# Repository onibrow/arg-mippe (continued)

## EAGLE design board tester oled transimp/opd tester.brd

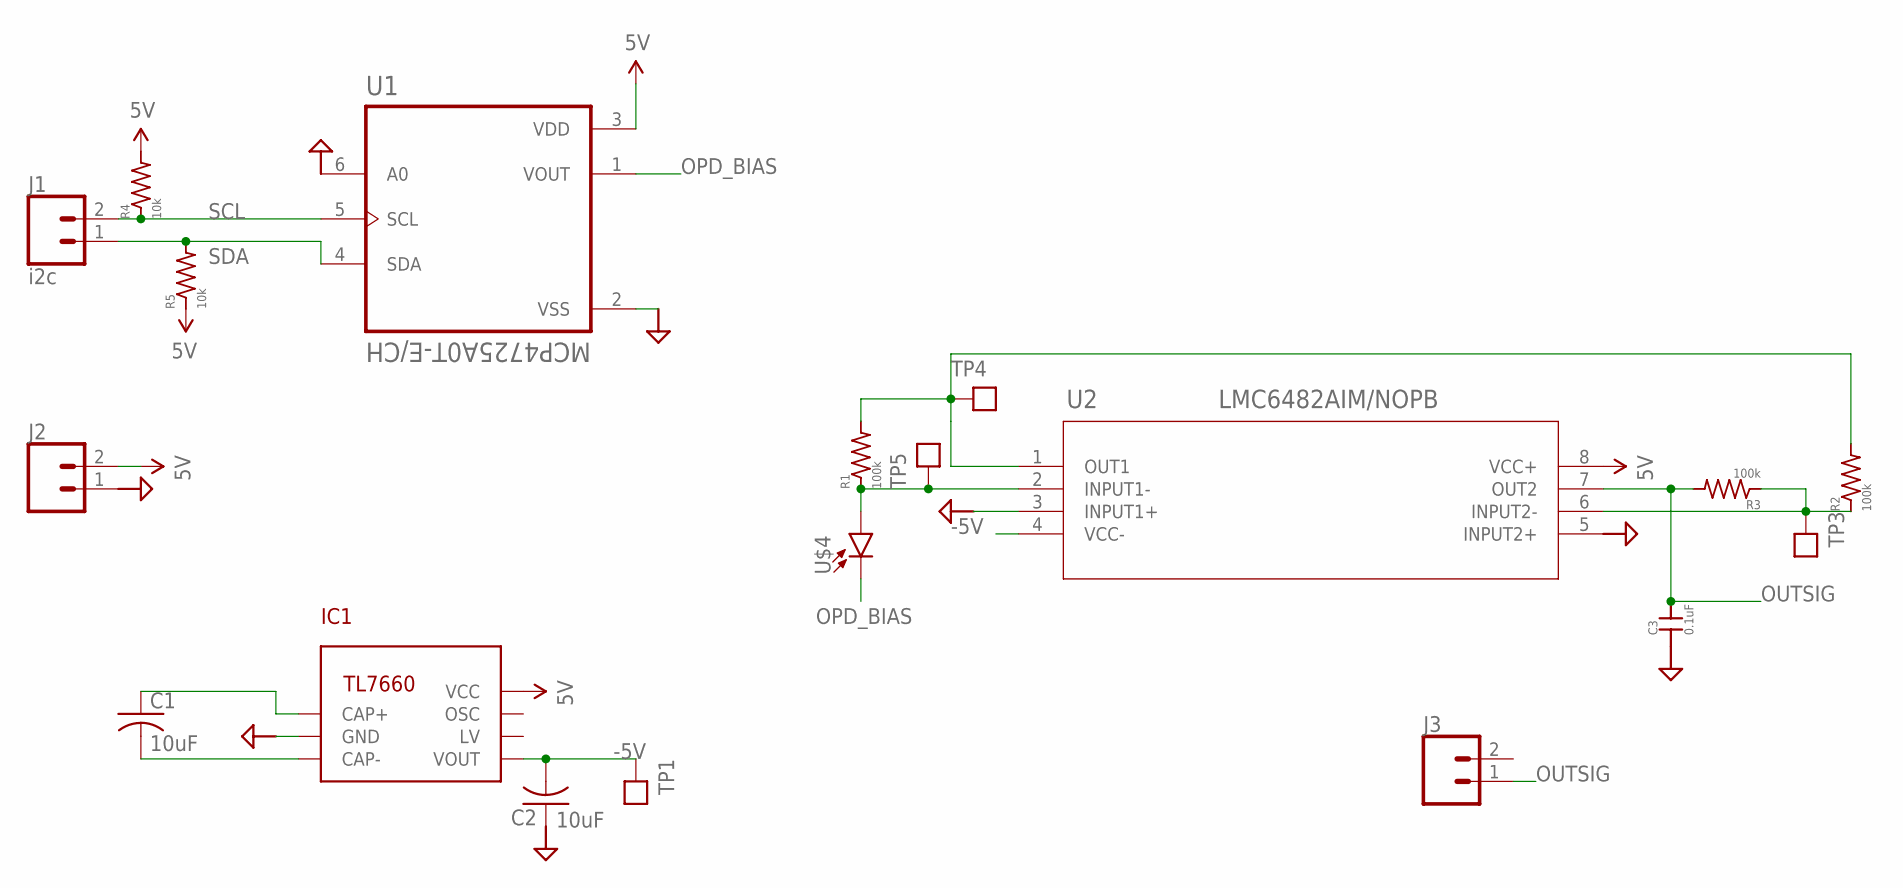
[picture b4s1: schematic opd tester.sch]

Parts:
C1, C2: 10uF; CAP_3MM
C3: 0.1uF; 0603-CAP
IC1: TL7660; 8SOICW
J1: i2c; 1X02
J2, J3: CONN_02; 1X02
R1, R2, R3: 100k; 0603-RES
R4, R5: 10k; 0603-RES
TP1, TP3, TP4, TP5: TEST_POINTTHRU; TEST_POINT
U1: MCP4725A0T-E/CH; SOT95P270X145-6N
U2: LMC6482AIM/NOPB; M08A
U$4: XDCR_SFH_229

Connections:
5V: IC1.8 (VCC), J2.2, R4.2, R5.1, U1.3 (VDD), U2.8 (VCC+)
-5V: C2.NEG, IC1.5 (VOUT), TP1.1, U2.4 (VCC-)
GND: C2.POS, C3.1, IC1.3 (GND), J2.1, U1.2 (VSS), U1.6 (A0), U2.3 (INPUT1+), U2.5 (INPUT2+)
unnamed: C1.POS, IC1.2 (CAP+)
unnamed: C1.NEG, IC1.4 (CAP-)
unnamed 5: R1.1, TP5.1, U2.2 (INPUT1-), U$4.1 (A); also elsewhere on the board
unnamed 6: R1.2, R2.2, TP4.1, U2.1 (OUT1); also elsewhere on the board
unnamed: R2.1, R3.1, TP3.1, U2.6 (INPUT2-)
OPD_BIAS: U1.1 (VOUT), U$4.2 (C)
OUTSIG: C3.2, J3.1, R3.2, U2.7 (OUT2)
SCL: J1.2, R4.1, U1.5 (SCL)
SDA: J1.1, R5.2, U1.4 (SDA)

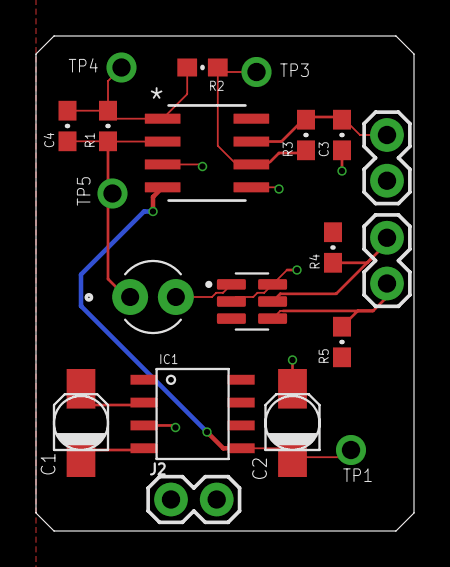
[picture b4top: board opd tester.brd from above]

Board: 2 copper layers, 21.0 x 27.5 mm, 20 parts (0 on the bottom side), 12 nets.

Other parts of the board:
C4: 0.1uF; 0603-CAP

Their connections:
unnamed 5: C4.1; also elsewhere on the board
unnamed 6: C4.2; also elsewhere on the board

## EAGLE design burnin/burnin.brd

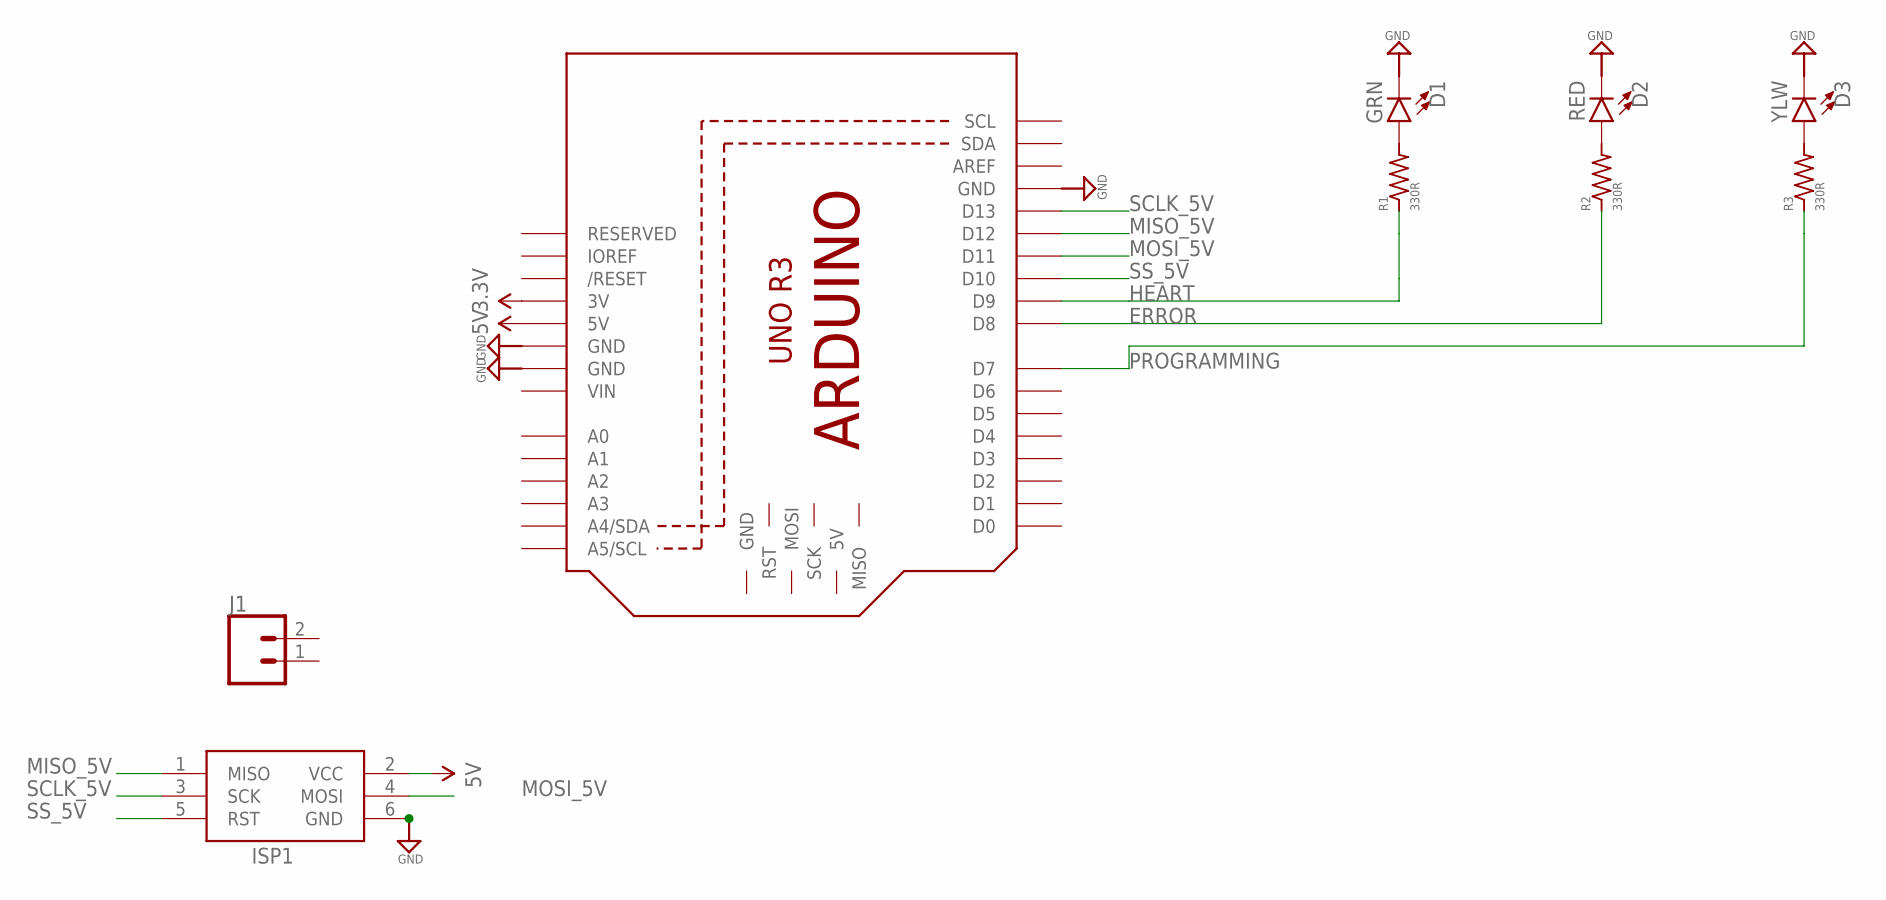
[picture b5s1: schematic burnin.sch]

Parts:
D1: GRN; LED-0603
D2: RED; LED-0603
D3: YLW; LED-0603
ISP1: AVRISP-6; AVRISP
J1: CONN_02; 1X02
M1: ARDUINO_R3_ICSP_NODIM; ARDUINOR3_ICSP_NODIM
R1, R2, R3: 330R; 0603-RES

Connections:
3.3V: M1.3V
5V: ISP1.2 (VCC), M1.5V
ERROR: M1.D8, R2.1
GND: D1.C, D2.C, D3.C, ISP1.6 (GND), M1.GND, M1.GND@1 (GND), M1.GND@3 (GND)
HEART: M1.D9, R1.1
MISO_5V: ISP1.1 (MISO), M1.D12
MOSI_5V: ISP1.4 (MOSI), M1.D11
unnamed: D1.A, R1.2
unnamed: D2.A, R2.2
unnamed: D3.A, R3.2
PROGRAMMING: M1.D7, R3.1
SCLK_5V: ISP1.3 (SCK), M1.D13
SS_5V: ISP1.5 (RST), M1.D10
VIN: M1.VIN

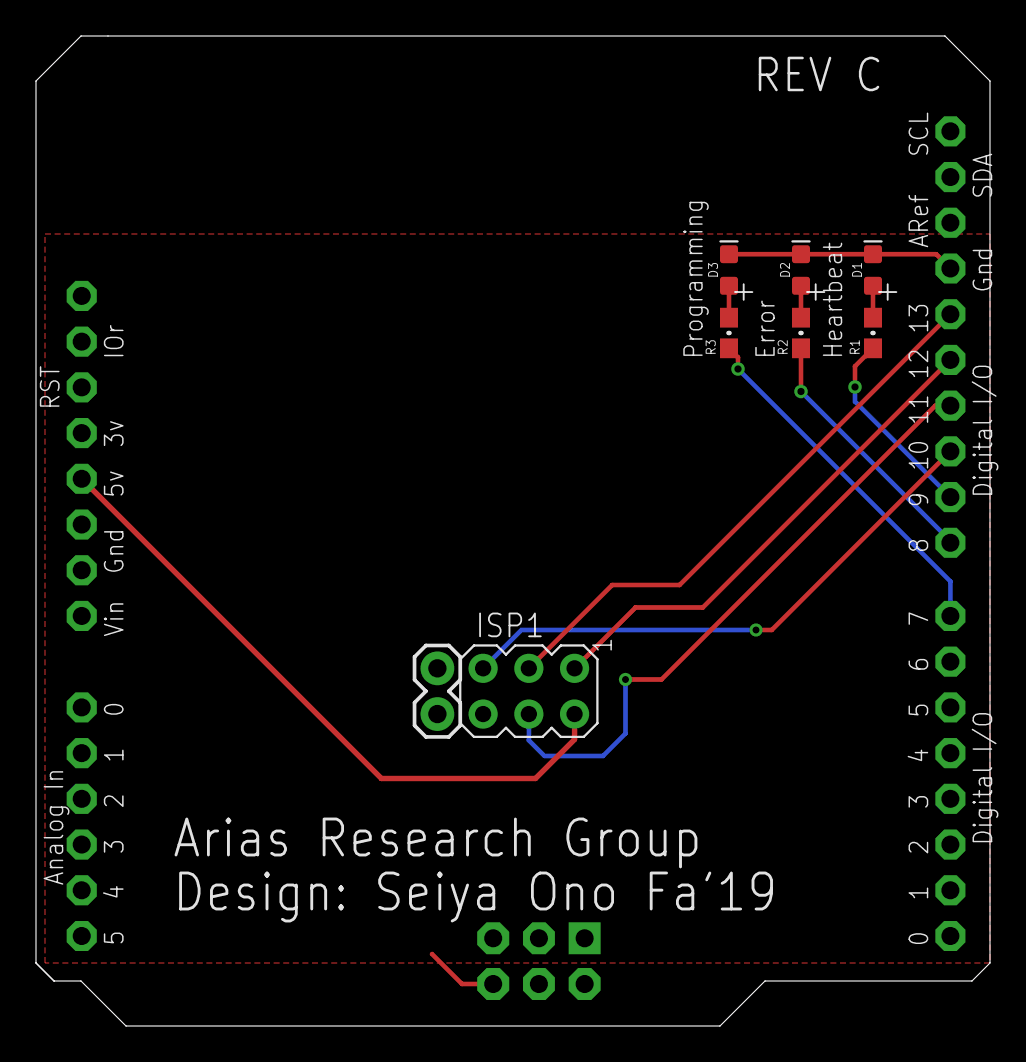
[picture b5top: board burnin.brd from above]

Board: 2 copper layers, 53.0 x 55.0 mm, 9 parts (0 on the bottom side), 12 nets.

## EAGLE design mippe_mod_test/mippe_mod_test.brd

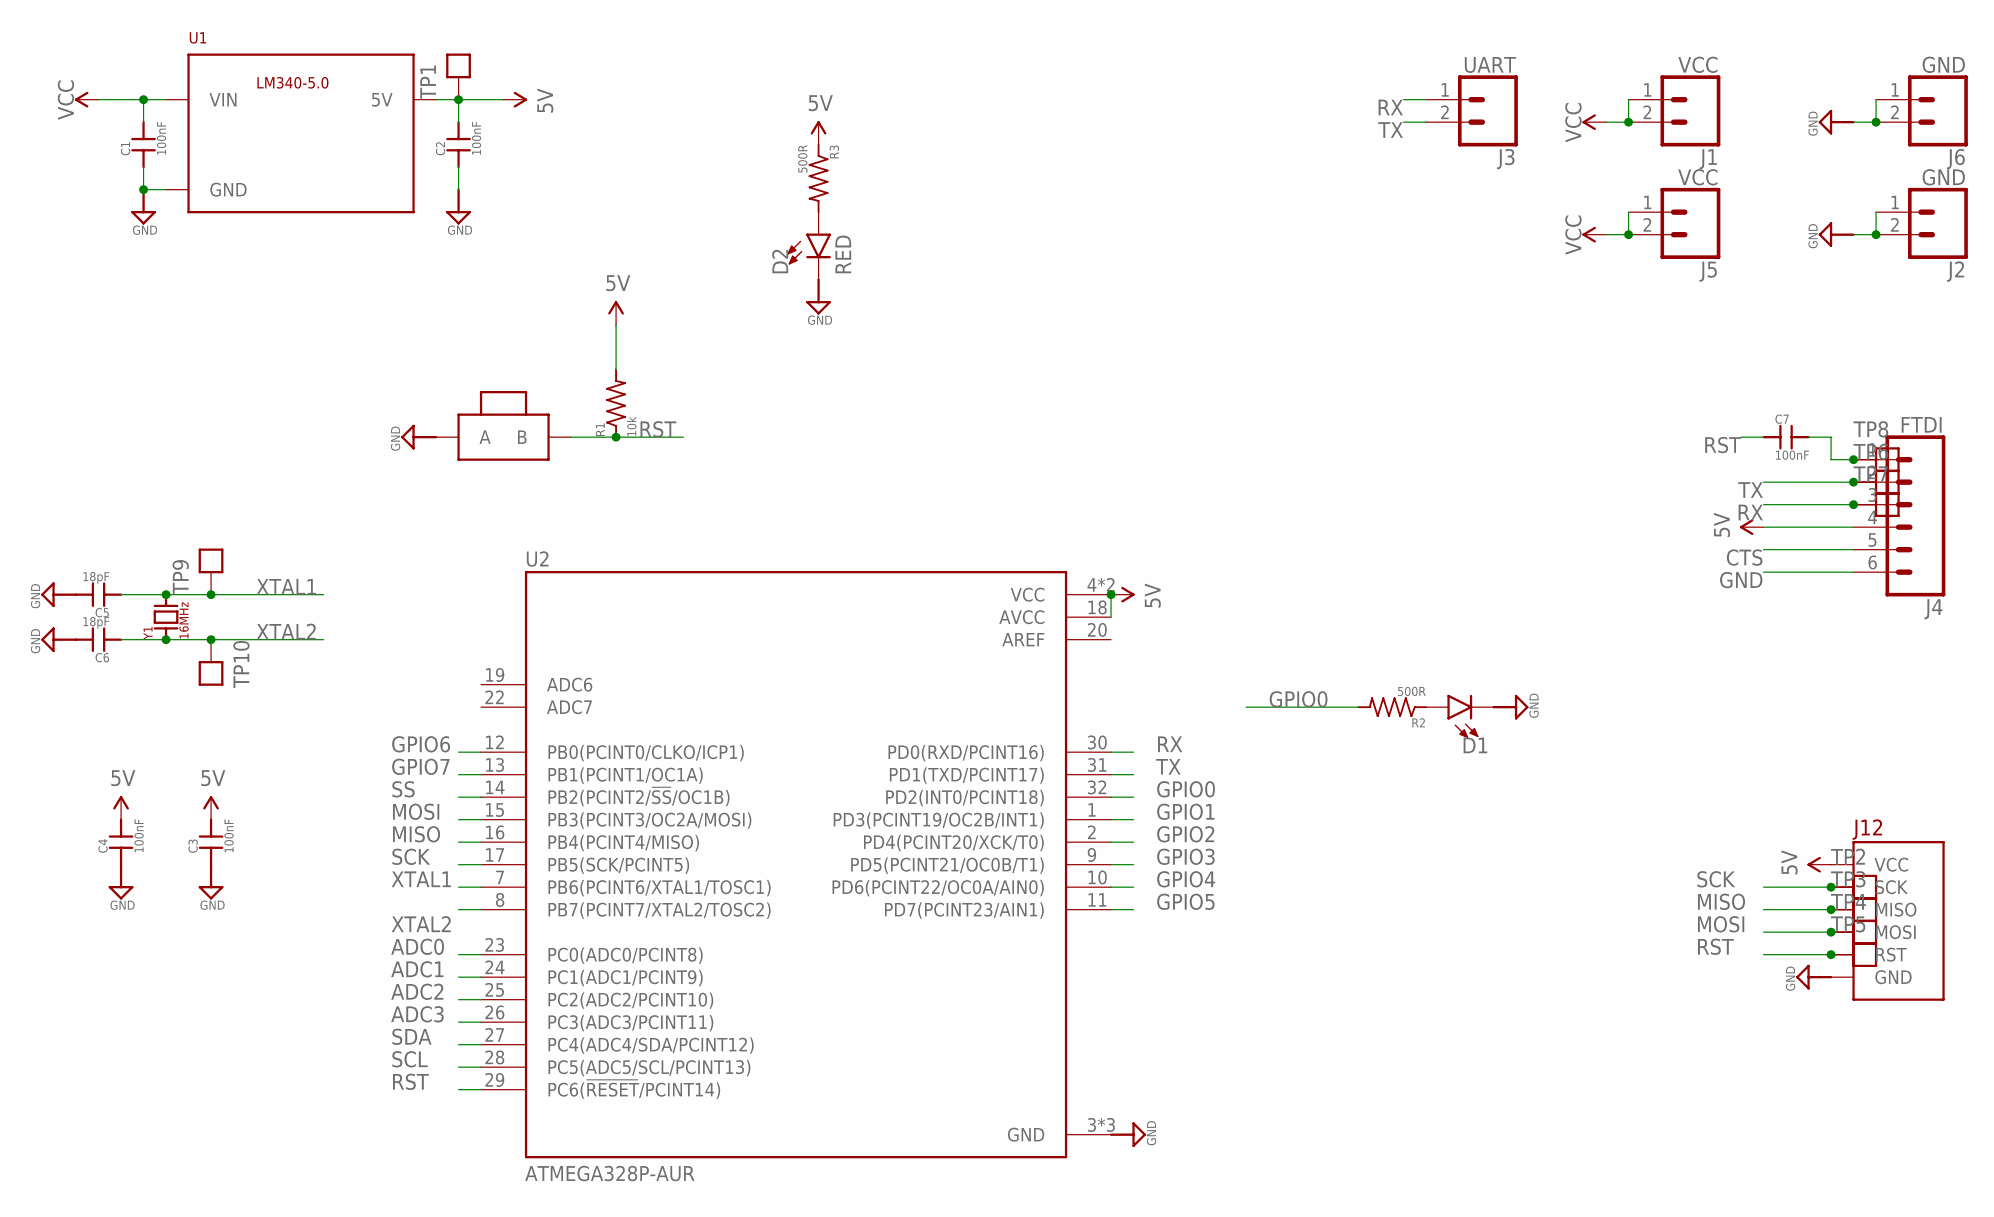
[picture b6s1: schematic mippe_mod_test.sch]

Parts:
C1, C2, C3, C4, C7: 100nF; 0402-CAP
C5, C6: 18pF; 0402-CAP
D1: LED0603; LED-0603
D2: RED; LED-0603
J1, J5: VCC; 1X02
J2, J6: GND; 1X02
J3: UART; 1X02
J4: FTDI; 1X06_NO_SILK
J12: BURNIN
R1: 10k; R0402
R2, R3: 500R; R0402
SW1: BTN-PTS810; BTN_PTS810
TP1, TP2, TP3, TP4, TP5, TP6, TP7, TP8, TP9, TP10: TEST_POINTTHRU; TEST_POINT
U1: LM340MPX-5.0230; SOT230P700X180-4N
U2: ATMEGA328P-AUR; QFP80P900X900X120-32N
Y1: 16MHz; XTAL500X320X130N

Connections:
5V: C2.2, C3.2, C4.2, J4.4, J12.3.3V (VCC), R1.2, R3.1, TP1.1, U1.3 (5V), U2.4 (VCC), U2.6 (VCC), U2.18 (AVCC)
ADC0: U2.23 (PC0(ADC0/PCINT8))
ADC1: U2.24 (PC1(ADC1/PCINT9))
ADC2: U2.25 (PC2(ADC2/PCINT10))
ADC3: U2.26 (PC3(ADC3/PCINT11))
AREF: U2.20 (AREF)
CTS: J4.5
GND: C1.1, C2.1, C3.1, C4.1, C5.2, C6.2, D1.C, D2.C, J2.1, J2.2, J4.6, J6.1, J6.2, J12.GND, SW1.1 (A), SW1.2 (A), U1.2 (GND), U1.4 (GND), U2.3 (GND), U2.5 (GND), U2.21 (GND)
GPIO0: R2.2, U2.32 (PD2(INT0/PCINT18))
GPIO1: U2.1 (PD3(PCINT19/OC2B/INT1))
GPIO2: U2.2 (PD4(PCINT20/XCK/T0))
GPIO3: U2.9 (PD5(PCINT21/OC0B/T1))
GPIO4: U2.10 (PD6(PCINT22/OC0A/AIN0))
GPIO5: U2.11 (PD7(PCINT23/AIN1))
GPIO6: U2.12 (PB0(PCINT0/CLKO/ICP1))
GPIO7: U2.13 (PB1(PCINT1/OC1A))
MISO: J12.MISO, TP3.1, U2.16 (PB4(PCINT4/MISO))
MOSI: J12.MOSI, TP4.1, U2.15 (PB3(PCINT3/OC2A/MOSI))
unnamed: D1.A, R2.1
unnamed: D2.A, R3.2
unnamed: C7.2, J4.1, TP8.1
RST: C7.1, J12.RST, R1.1, SW1.3 (B), SW1.4 (B), TP5.1, U2.29 (PC6(!RESET!/PCINT14))
RX: J3.1, J4.3, TP7.1, U2.30 (PD0(RXD/PCINT16))
SCK: J12.SCK, TP2.1, U2.17 (PB5(SCK/PCINT5))
SCL: U2.28 (PC5(ADC5/SCL/PCINT13))
SDA: U2.27 (PC4(ADC4/SDA/PCINT12))
SS: U2.14 (PB2(PCINT2/!SS!/OC1B))
TX: J3.2, J4.2, TP6.1, U2.31 (PD1(TXD/PCINT17))
VCC: C1.2, J1.1, J1.2, J5.1, J5.2, U1.1 (VIN)
XTAL1: C5.1, TP9.1, U2.7 (PB6(PCINT6/XTAL1/TOSC1)), Y1.2 (B)
XTAL2: C6.1, TP10.1, U2.8 (PB7(PCINT7/XTAL2/TOSC2)), Y1.1 (A)

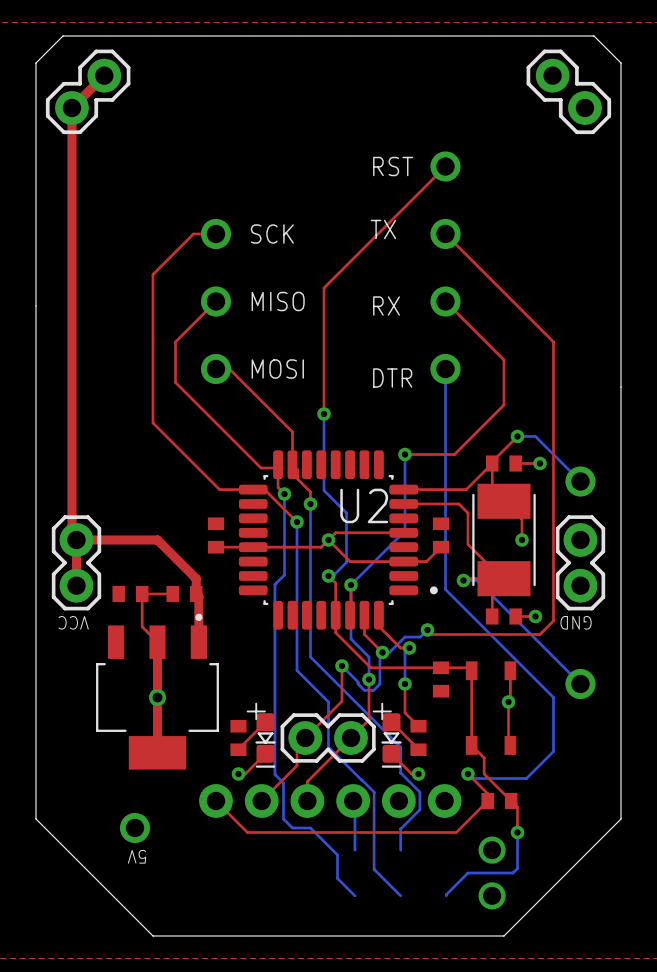
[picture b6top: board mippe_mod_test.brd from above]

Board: 2 copper layers, 32.5 x 50.0 mm, 33 parts (0 on the bottom side), 15 nets.

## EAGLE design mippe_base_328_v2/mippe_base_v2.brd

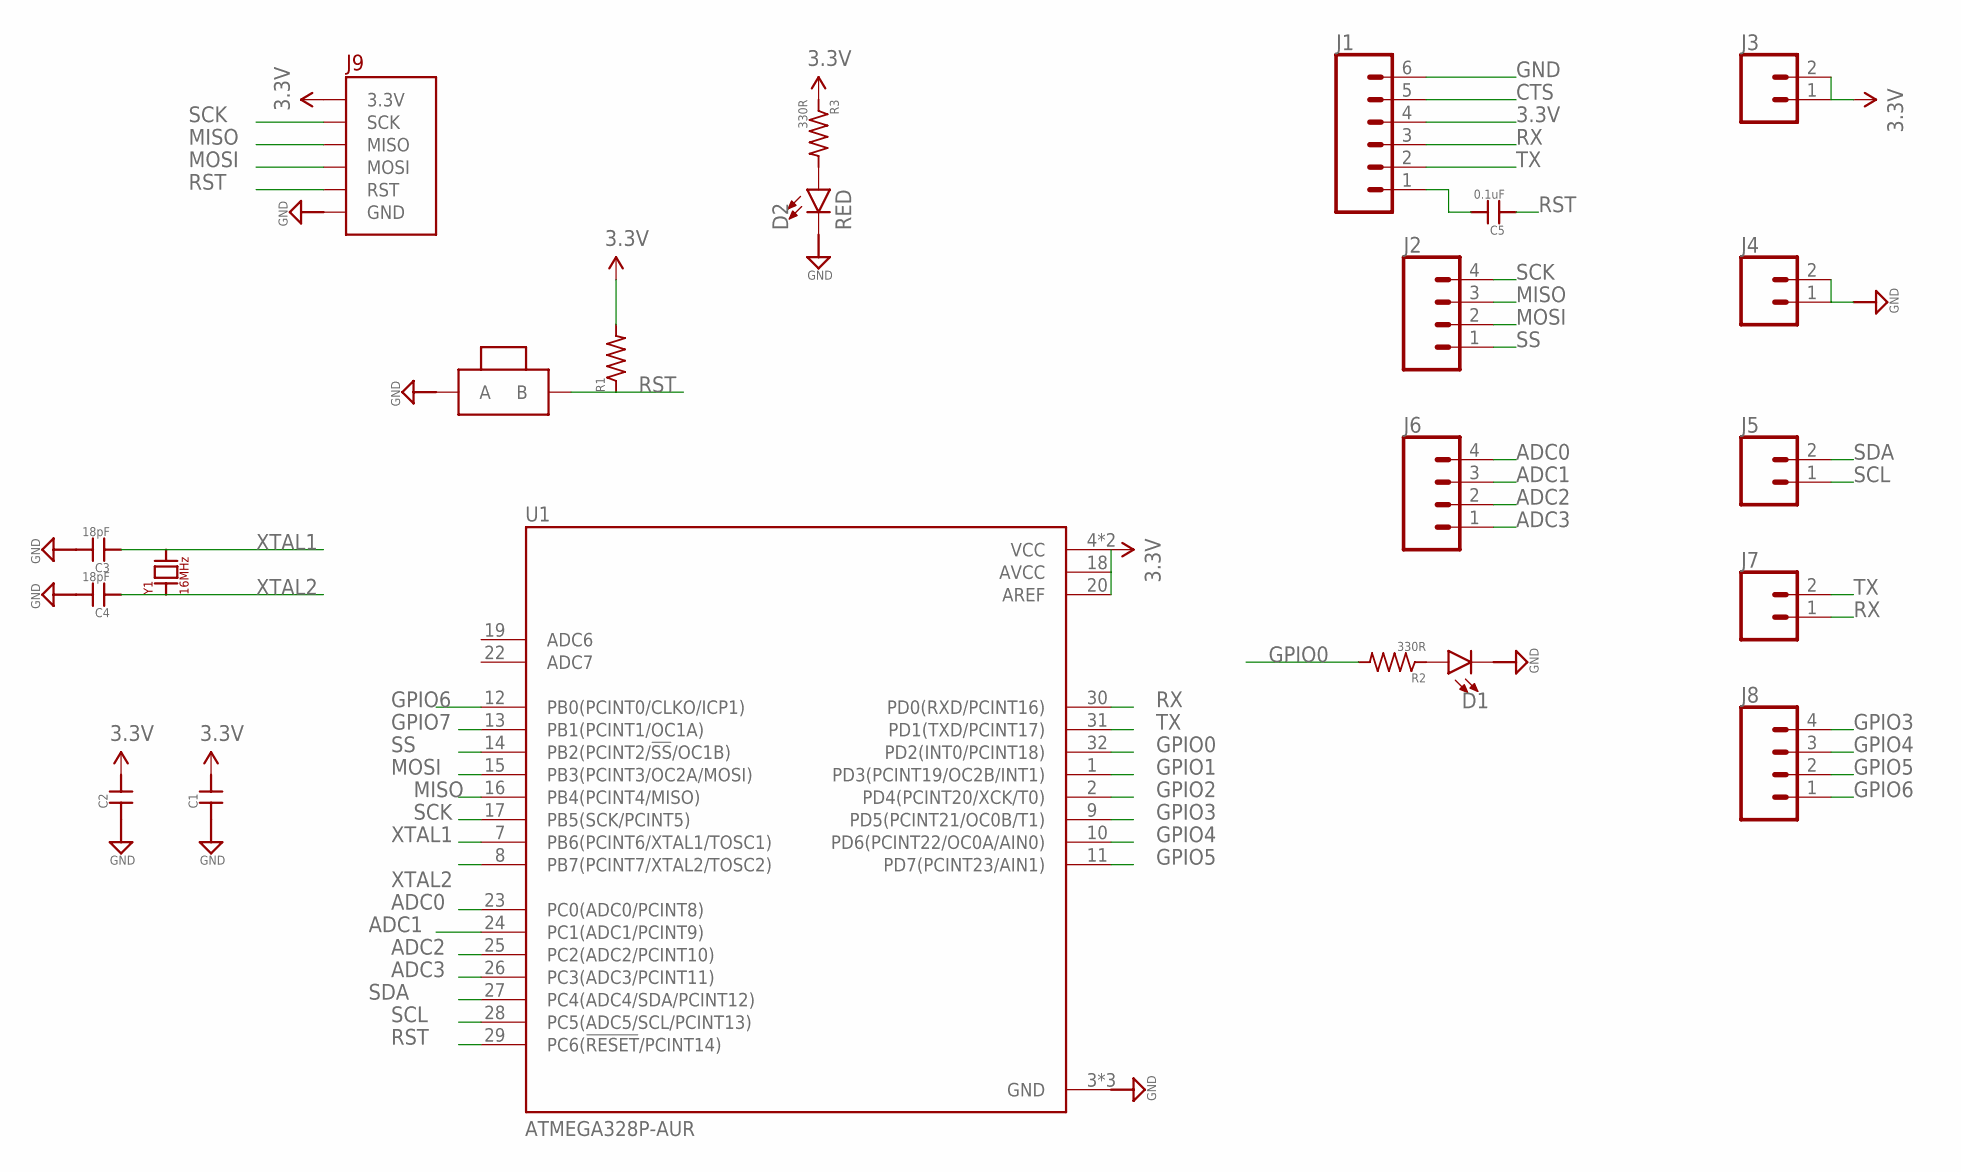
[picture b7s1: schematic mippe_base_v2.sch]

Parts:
C1, C2: CAP0603-CAP; 0603-CAP
C3, C4: 18pF; 0603-CAP
C5: 0.1uF; 0603-CAP
D1: LED0603; LED-0603
D2: RED; LED-0603
J1: CONN_06NO_SILK_FEMALE_PTH; 1X06_NO_SILK
J2, J6, J8: CONN_041X04_NO_SILK; 1X04_NO_SILK
J3, J4, J5, J7: CONN_021X02_NO_SILK; 1X02_NO_SILK
J9: BURNIN
R1: R-US_R0603; R0603
R2, R3: 330R; R0603
SW1: BTN-PTS810; BTN_PTS810
U1: ATMEGA328P-AUR; QFP80P900X900X120-32N
Y1: 16MHz; XTAL500X320X130N

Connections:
3.3V: C1.2, C2.2, J1.4, J3.1, J3.2, J9.3.3V, R1.2, R3.1, U1.4 (VCC), U1.6 (VCC), U1.18 (AVCC), U1.20 (AREF)
ADC0: J6.4, U1.23 (PC0(ADC0/PCINT8))
ADC1: J6.3, U1.24 (PC1(ADC1/PCINT9))
ADC2: J6.2, U1.25 (PC2(ADC2/PCINT10))
ADC3: J6.1, U1.26 (PC3(ADC3/PCINT11))
CTS: J1.5
GND: C1.1, C2.1, C3.2, C4.2, D1.C, D2.C, J1.6, J4.1, J4.2, J9.GND, SW1.1 (A), SW1.2 (A), U1.3 (GND), U1.5 (GND), U1.21 (GND)
GPIO0: R2.2, U1.32 (PD2(INT0/PCINT18))
GPIO1: U1.1 (PD3(PCINT19/OC2B/INT1))
GPIO2: U1.2 (PD4(PCINT20/XCK/T0))
GPIO3: J8.4, U1.9 (PD5(PCINT21/OC0B/T1))
GPIO4: J8.3, U1.10 (PD6(PCINT22/OC0A/AIN0))
GPIO5: J8.2, U1.11 (PD7(PCINT23/AIN1))
GPIO6: J8.1, U1.12 (PB0(PCINT0/CLKO/ICP1))
GPIO7: U1.13 (PB1(PCINT1/OC1A))
MISO: J2.3, J9.MISO, U1.16 (PB4(PCINT4/MISO))
MOSI: J2.2, J9.MOSI, U1.15 (PB3(PCINT3/OC2A/MOSI))
unnamed: D1.A, R2.1
unnamed: D2.A, R3.2
unnamed: C5.2, J1.1
RST: C5.1, J9.RST, R1.1, SW1.3 (B), SW1.4 (B), U1.29 (PC6(!RESET!/PCINT14))
RX: J1.3, J7.1, U1.30 (PD0(RXD/PCINT16))
SCK: J2.4, J9.SCK, U1.17 (PB5(SCK/PCINT5))
SCL: J5.1, U1.28 (PC5(ADC5/SCL/PCINT13))
SDA: J5.2, U1.27 (PC4(ADC4/SDA/PCINT12))
SS: J2.1, U1.14 (PB2(PCINT2/!SS!/OC1B))
TX: J1.2, J7.2, U1.31 (PD1(TXD/PCINT17))
XTAL1: C3.1, U1.7 (PB6(PCINT6/XTAL1/TOSC1)), Y1.2 (B)
XTAL2: C4.1, U1.8 (PB7(PCINT7/XTAL2/TOSC2)), Y1.1 (A)

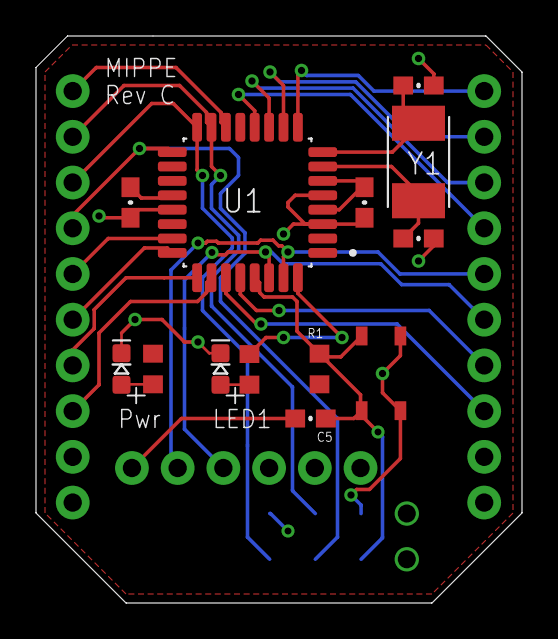
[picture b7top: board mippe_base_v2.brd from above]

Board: 2 copper layers, 27.0 x 31.5 mm, 22 parts (0 on the bottom side), 25 nets.

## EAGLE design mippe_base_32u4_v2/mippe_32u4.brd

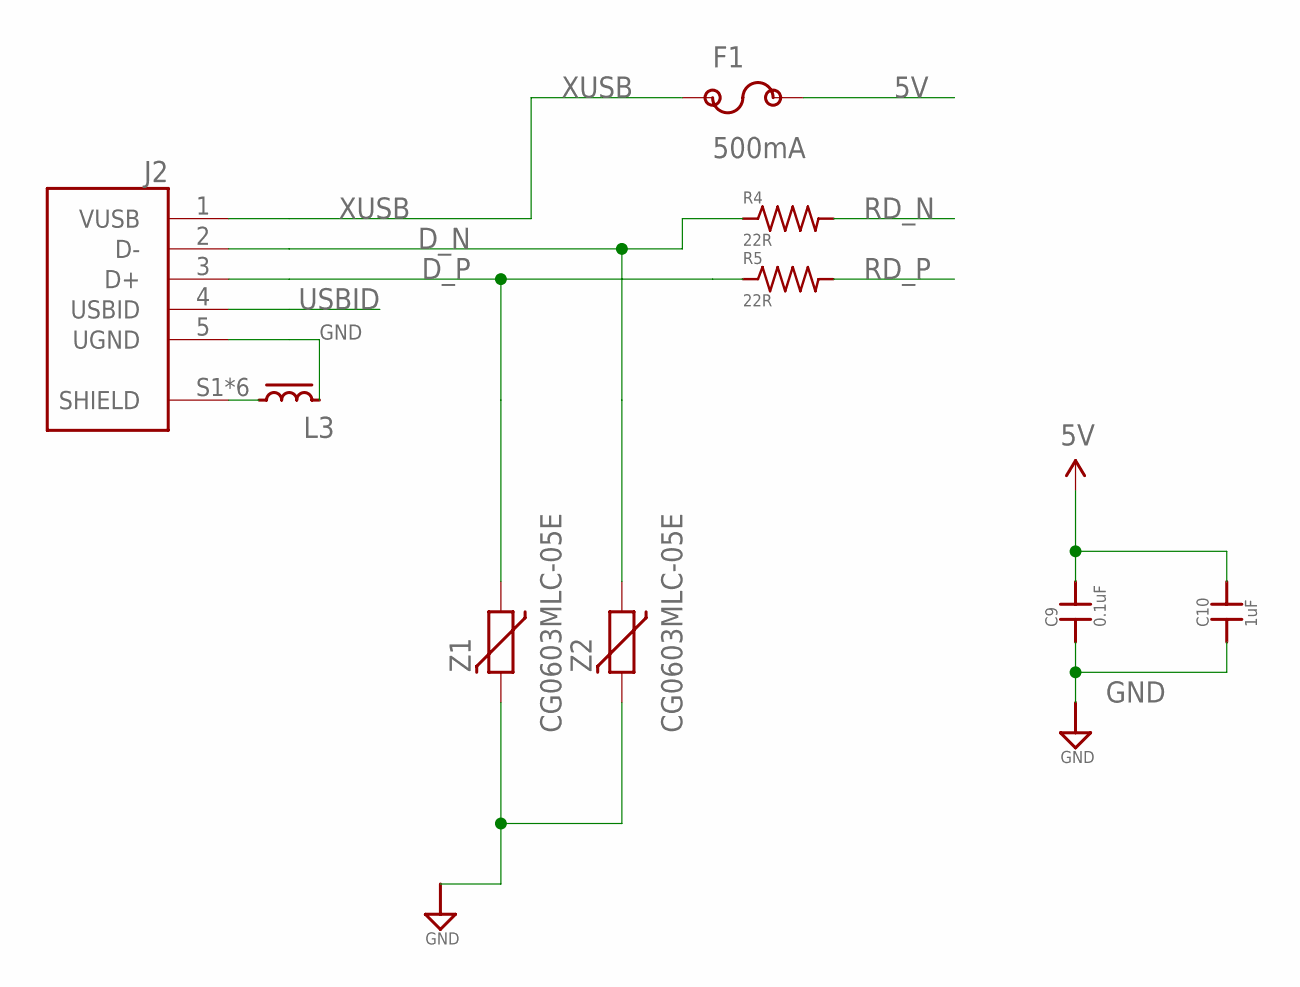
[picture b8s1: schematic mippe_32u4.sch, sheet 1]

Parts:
C9: 0.1uF; 0402-CAP
C10: 1uF; 0402-CAP
F1: 500mA; 1206
J2: USB; FCI_10103594-0001LF
L3: IND; IND_2012
R4, R5: 22R; R0402
Z1, Z2: CG0603MLC-05E; 0603-RES

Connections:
5V: C9.2, C10.2, F1.2; also elsewhere on the board
D_N: J2.2 (D-), R4.1, Z2.1
D_P: J2.3 (D+), R5.1, Z1.1
GND: C9.1, C10.1, J2.5 (UGND), L3.2, Z1.2, Z2.2; also elsewhere on the board
RD_N: R4.2; also elsewhere on the board
RD_P: R5.2; also elsewhere on the board
SHIELD: J2.S1 (SHIELD), J2.S2 (SHIELD), J2.S3 (SHIELD), J2.S4 (SHIELD), J2.S5 (SHIELD), J2.S6 (SHIELD), L3.1
USBID: J2.4 (USBID)
XUSB: F1.1, J2.1 (VUSB)

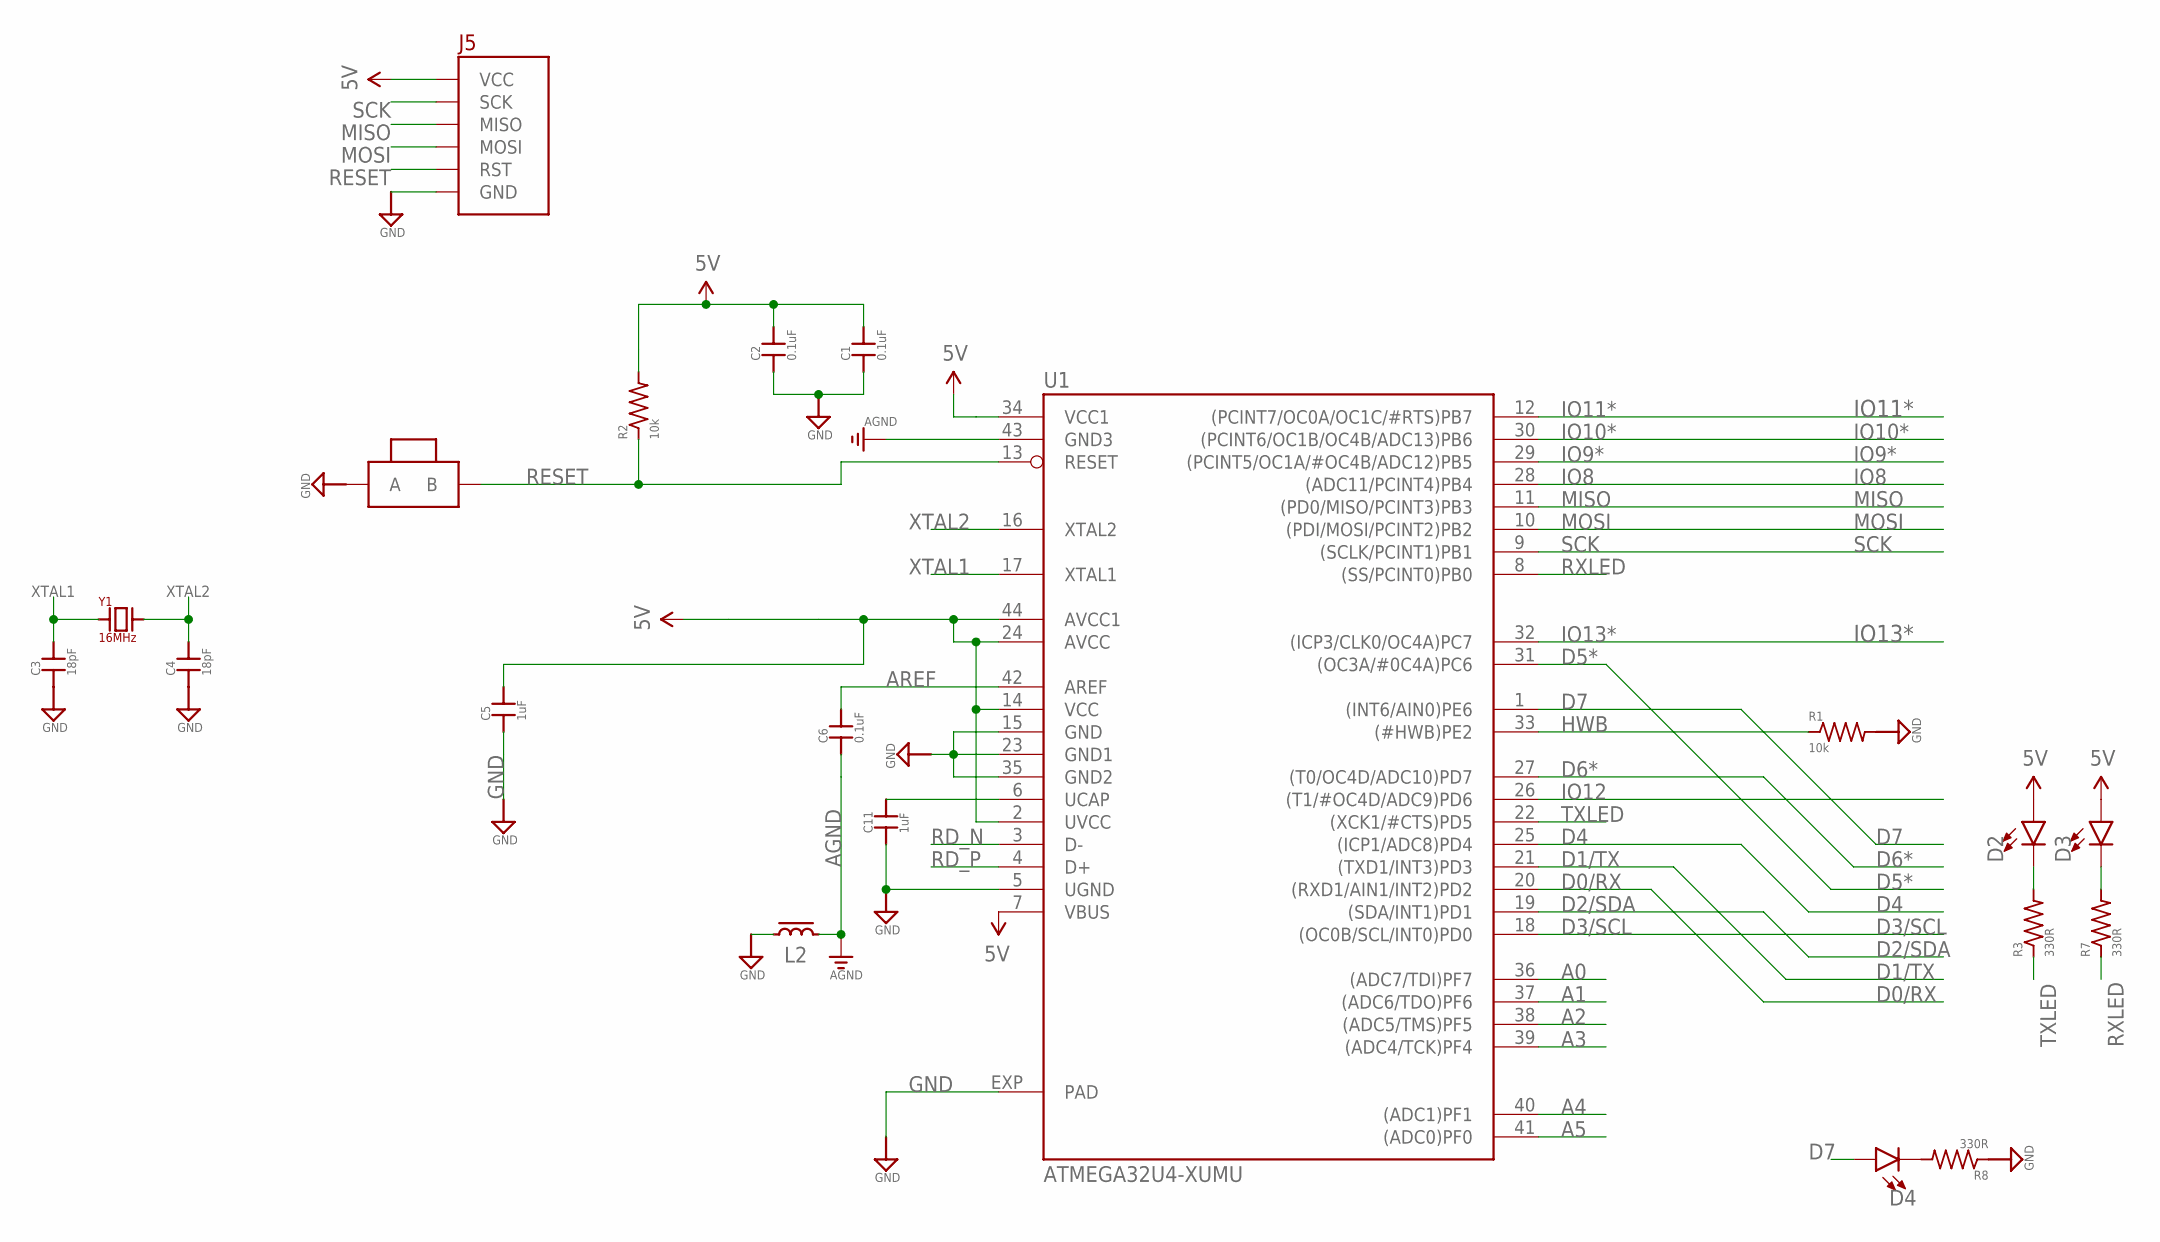
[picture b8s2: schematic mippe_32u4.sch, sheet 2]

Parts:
C1, C2, C6: 0.1uF; 0402-CAP
C3, C4: 18pF; 0402-CAP
C5, C11: 1uF; 0402-CAP
D2, D3, D4: LED0603; LED-0603
J5: BURNIN
L2: IND; IND_2012
R1, R2: 10k; R0402
R3, R7, R8: 330R; R0402
SW1: BTN-PTS810; BTN_PTS810
U1: ATMEGA32U4-XUMU; QFN44ML7X7
Y1: 16MHz; XTAL500X320X130N

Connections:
5V: C1.2, C2.2, C5.2, D2.A, D3.A, J5.3.3V (VCC), R2.2, U1.2 (UVCC), U1.7 (VBUS), U1.14 (VCC), U1.24 (AVCC), U1.34 (VCC1), U1.44 (AVCC1); also elsewhere on the board
A0: U1.36 ((ADC7/TDI)PF7)
A1: U1.37 ((ADC6/TDO)PF6)
A2: U1.38 ((ADC5/TMS)PF5)
A3: U1.39 ((ADC4/TCK)PF4)
A4: U1.40 ((ADC1)PF1)
A5: U1.41 ((ADC0)PF0)
AGND: C6.1, L2.2, U1.43 (GND3)
AREF: C6.2, U1.42 (AREF)
D0/RX: U1.20 ((RXD1/AIN1/INT2)PD2)
D1/TX: U1.21 ((TXD1/INT3)PD3)
D2/SDA: U1.19 ((SDA/INT1)PD1)
D3/SCL: U1.18 ((OC0B/SCL/INT0)PD0)
D4: U1.25 ((ICP1/ADC8)PD4)
D5*: U1.31 ((OC3A/#0C4A)PC6)
D6*: U1.27 ((T0/OC4D/ADC10)PD7)
D7: D4.A, U1.1 ((INT6/AIN0)PE6)
GND: C1.1, C2.1, C3.1, C4.1, C5.1, C11.1, J5.GND, L2.1, R1.2, R8.1, SW1.1 (A), SW1.2 (A), U1.5 (UGND), U1.15 (GND), U1.23 (GND1), U1.35 (GND2), U1.EXP (PAD); also elsewhere on the board
HWB: R1.1, U1.33 ((#HWB)PE2)
IO8: U1.28 ((ADC11/PCINT4)PB4)
IO9*: U1.29 ((PCINT5/OC1A/#OC4B/ADC12)PB5)
IO10*: U1.30 ((PCINT6/OC1B/OC4B/ADC13)PB6)
IO11*: U1.12 ((PCINT7/OC0A/OC1C/#RTS)PB7)
IO12: U1.26 ((T1/#OC4D/ADC9)PD6)
IO13*: U1.32 ((ICP3/CLK0/OC4A)PC7)
MISO: J5.MISO, U1.11 ((PD0/MISO/PCINT3)PB3)
MOSI: J5.MOSI, U1.10 ((PDI/MOSI/PCINT2)PB2)
unnamed: D2.C, R3.2
unnamed: D3.C, R7.2
unnamed: D4.C, R8.2
RD_N: U1.3 (D-); also elsewhere on the board
RD_P: U1.4 (D+); also elsewhere on the board
RESET: J5.RST, R2.1, SW1.3 (B), SW1.4 (B), U1.13 (RESET)
RXLED: R7.1, U1.8 ((SS/PCINT0)PB0)
SCK: J5.SCK, U1.9 ((SCLK/PCINT1)PB1)
TXLED: R3.1, U1.22 ((XCK1/#CTS)PD5)
UCAP: C11.2, U1.6 (UCAP)
XTAL1: C3.2, U1.17 (XTAL1), Y1.1 (A)
XTAL2: C4.2, U1.16 (XTAL2), Y1.2 (B)

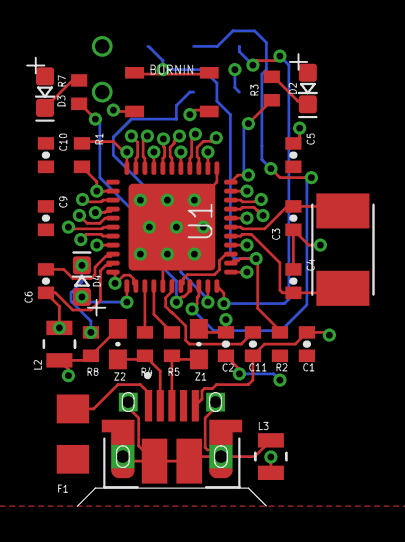
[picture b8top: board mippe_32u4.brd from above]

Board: 2 copper layers, 29 parts (0 on the bottom side), 24 nets.

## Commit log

2019-09-09 Initialize Repo
    Add gitignore
2019-09-09 Finish burnin shield, start base
2019-09-10 Finish burnin and mippe controller
2019-09-30 Add instructions to flash
2019-10-01 fix burnin OE and make QFP MIPPE
2019-10-18 fix rst and flip conn
2019-10-22 start 32u4
2019-10-23 more library conversion
2019-10-30 Progress on layout
2019-10-30 blah
2019-10-31 layout more
2019-11-02 finish 32u4 and rev c burnin
2019-11-02 Add same pinpouts as mipp_v2
2019-11-06 Add files for jlc order
2019-11-07 Update cpl for usb resistors
2019-11-25 add a bootloader burning script
2019-12-16 update jlc drc
2019-12-17 start compact design
2020-01-05 32u4 0402 rev
2020-01-11 rename original bases
2020-01-11 start oled pmic
2020-01-11 Start on the board
2020-01-11 layout board
2020-01-13 place order
2020-01-23 fix fill
2020-02-03 Start transimp section
2020-02-04 start the 328 mod and adc
2020-02-06 finish module and diff module
2020-02-06 finish bom cpl for mippe mod and adc diff
2020-02-08 start opd test and create firmware for oleds
2020-02-14 more work
2020-02-19 start mobo
2020-02-20 more mobo work
2020-02-20 mobo work
2020-02-21 Fix bootloader script and add calibration to pwm tester for quick voltage setting
2020-02-21 test setup with 9V
2020-02-22 more progress add ss
2020-02-24 finalize mobo
2020-02-27 start passive potentiometric sensor
2020-02-27 start oled pmic module
2020-02-27 finish oled module
2020-02-27 update burnin drill size
2020-02-28 blaaahhhhh 328pb worked
2020-02-28 add cap for stabalization
2020-02-28 add more ground pins to mobo
2020-02-29 finish transimp module
2020-03-01 finish boms and cams
2020-03-01 Fix all boms and cpls
2020-03-03 add 328pb
2020-03-10 add test sketch for mippe modules
2020-03-13 good start on oled firmware
2020-03-13 add a tester ino
2020-03-13 good start on transimp driver
2020-03-13 two new types of pas pot firmware with dig pot contorl
2020-03-23 place final order for mobo
2020-03-23 move test board to transimp
2020-03-23 big clean
2020-03-24 write more firmware
2020-03-25 start on oled driver ui
2020-03-26 reorg ui files
2020-03-26 rename serial file
2020-03-26 finish scheduler code for oleds
2020-03-30 lots of tia progress
2020-03-31 first our of integration done
2020-04-01 first rev of mippe ui
2020-04-01 change to buff polling
2020-04-02 finished ???
2020-04-02 finish!
2020-04-07 ignore csv files
2020-04-07 Add modules for each
2020-04-07 Add template firmware and creates higher classes
2020-04-08 clean up class structure
2020-04-20 fix some small period bug
